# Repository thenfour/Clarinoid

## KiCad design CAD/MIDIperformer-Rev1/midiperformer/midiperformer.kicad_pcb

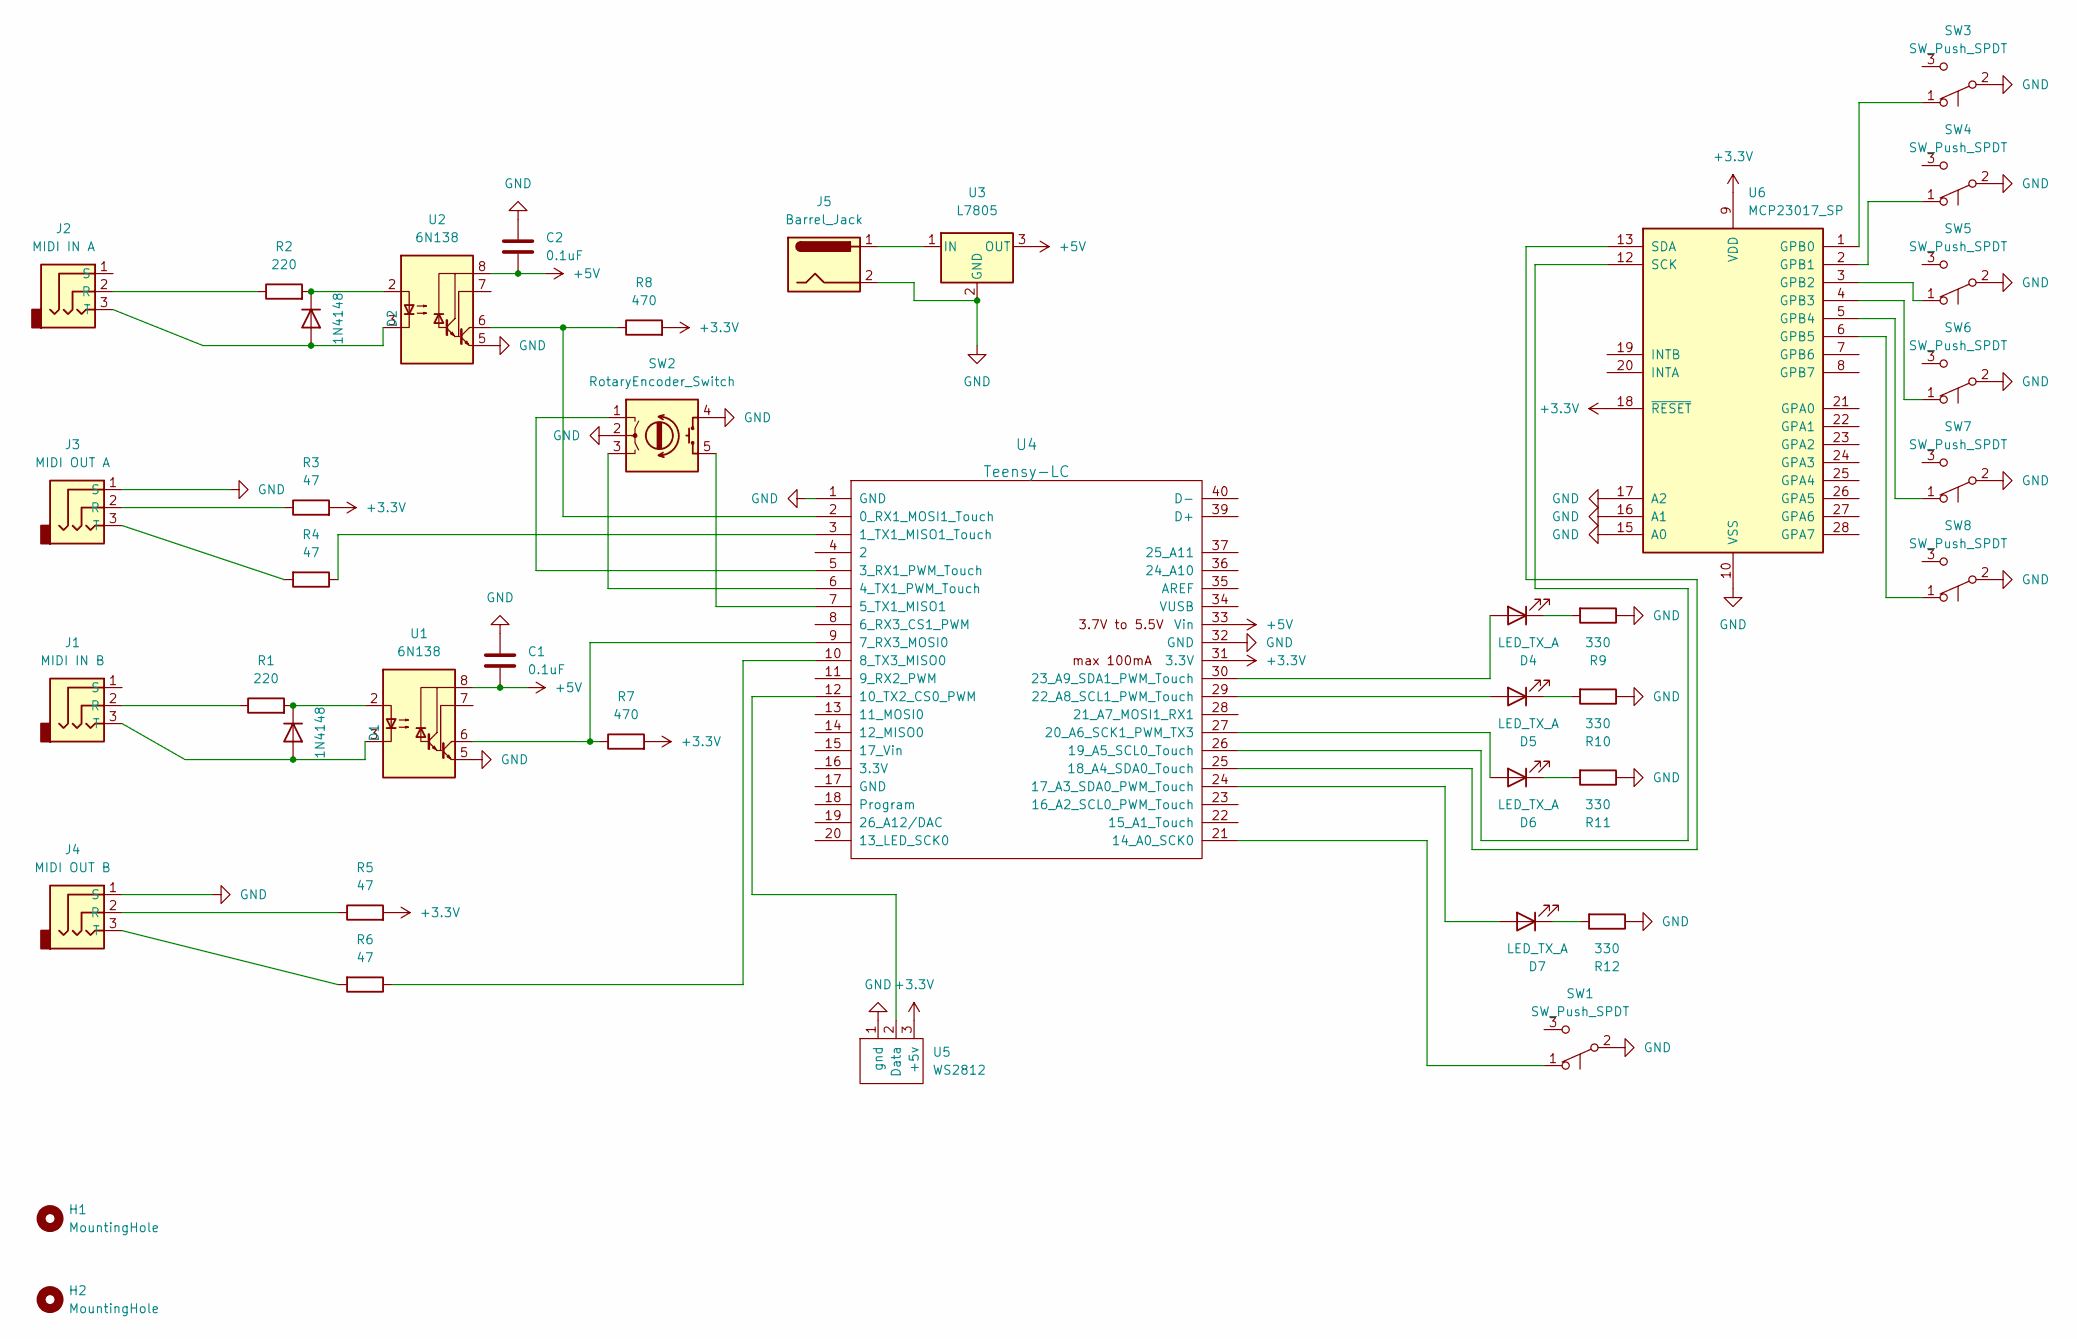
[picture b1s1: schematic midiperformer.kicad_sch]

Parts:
C1, C2: 0.1uF; C_Disc_D3.8mm_W2.6mm_P2.50mm
D1, D2: 1N4148; D_DO-35_SOD27_P7.62mm_Horizontal
D4, D5, D6, D7: LED_TX_A; SolderWire-0.25sqmm_1x02_P4.2mm_D0.65mm_OD1.7mm
H1, H2: MountingHole; MountingHole_2.7mm_M2.5_ISO14580_Pad
J1: MIDI IN B; SolderWire-0.25sqmm_1x03_P4.2mm_D0.65mm_OD1.7mm
J2: MIDI IN A; SolderWire-0.25sqmm_1x03_P4.2mm_D0.65mm_OD1.7mm
J3: MIDI OUT A; SolderWire-0.25sqmm_1x03_P4.2mm_D0.65mm_OD1.7mm
J4: MIDI OUT B; SolderWire-0.25sqmm_1x03_P4.2mm_D0.65mm_OD1.7mm
J5: Barrel_Jack; SolderWire-0.25sqmm_1x02_P4.2mm_D0.65mm_OD1.7mm
R1, R2: 220; R_Axial_DIN0207_L6.3mm_D2.5mm_P10.16mm_Horizontal
R3, R4, R5, R6: 47; R_Axial_DIN0207_L6.3mm_D2.5mm_P10.16mm_Horizontal
R7, R8: 470; R_Axial_DIN0207_L6.3mm_D2.5mm_P10.16mm_Horizontal
R9, R10, R11, R12: 330; R_Axial_DIN0207_L6.3mm_D2.5mm_P10.16mm_Horizontal
SW1, SW3, SW4, SW5, SW6, SW7, SW8: SW_Push_SPDT; SolderWire-0.25sqmm_1x02_P4.5mm_D0.65mm_OD2mm
SW2: RotaryEncoder_Switch; SolderWire-0.25sqmm_1x05_P4.2mm_D0.65mm_OD1.7mm
U1, U2: 6N138; DIP-8_W7.62mm
U3: L7805; TO-220-3_Vertical
U4: Teensy-LC; Teensy_LC
U5: WS2812; SolderWire-0.25sqmm_1x03_P4.2mm_D0.65mm_OD1.7mm
U6: MCP23017_SP; DIP-28_W7.62mm

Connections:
+3V3: R3.2, R5.2, R7.2, R8.2, U4.31 (3.3V), U5.3 (+5v), U6.9 (VDD), U6.18 (~RESET)
+5V: C1.1, C2.1, U1.8 (VCC), U2.8 (VCC), U3.3 (OUT), U4.33 (Vin)
GND: C1.2, C2.2, J3.1 (S), J4.1 (S), J5.2, R9.1, R10.1, R11.1, R12.1, SW1.2 (B), SW2.2 (GND), SW2.4 (SWGND), SW3.2 (B), SW4.2 (B), SW5.2 (B), SW6.2 (B), SW7.2 (B), SW8.2 (B), U1.5 (GND), U2.5 (GND), U3.2 (GND), U4.1 (GND), U4.32 (GND), U5.1 (gnd), U6.10 (VSS), U6.15 (A0), U6.16 (A1), U6.17 (A2)
unnamed: D1.1 (K), R1.2, U1.2 (C1)
unnamed: D1.2 (A), J1.3 (T), U1.3 (C2)
unnamed: D2.1 (K), R2.2, U2.2 (C1)
unnamed: D2.2 (A), J2.3 (T), U2.3 (C2)
unnamed: D4.1 (K), R9.2
unnamed: D4.2 (A), U4.30 (23_A9_SDA1_PWM_Touch)
unnamed: D5.1 (K), R10.2
unnamed: D5.2 (A), U4.29 (22_A8_SCL1_PWM_Touch)
unnamed: D6.1 (K), R11.2
unnamed: D6.2 (A), U4.27 (20_A6_SCK1_PWM_TX3)
unnamed: D7.1 (K), R12.2
unnamed: D7.2 (A), U4.24 (17_A3_SDA0_PWM_Touch)
unnamed: J1.2 (R), R1.1
unnamed: J2.2 (R), R2.1
unnamed: J3.2 (R), R3.1
unnamed: J3.3 (T), R4.2
unnamed: J4.2 (R), R5.1
unnamed: J4.3 (T), R6.2
unnamed: J5.1, U3.1 (IN)
unnamed: R4.1, U4.3 (1_TX1_MISO1_Touch)
unnamed: R6.1, U4.10 (8_TX3_MISO0)
unnamed: R7.1, U1.6 (VO2), U4.9 (7_RX3_MOSI0)
unnamed: R8.1, U2.6 (VO2), U4.2 (0_RX1_MOSI1_Touch)
unnamed: SW1.1 (A), U4.21 (14_A0_SCK0)
unnamed: SW2.1 (A), U4.5 (3_RX1_PWM_Touch)
unnamed: SW2.3 (B), U4.6 (4_TX1_PWM_Touch)
unnamed: SW2.5 (SW), U4.7 (5_TX1_MISO1)
unnamed: SW3.1 (A), U6.1 (GPB0)
unnamed: SW4.1 (A), U6.2 (GPB1)
unnamed: SW5.1 (A), U6.3 (GPB2)
unnamed: SW6.1 (A), U6.4 (GPB3)
unnamed: SW7.1 (A), U6.5 (GPB4)
unnamed: SW8.1 (A), U6.6 (GPB5)
unnamed: U4.12 (10_TX2_CS0_PWM), U5.2 (Data)
unnamed: U4.25 (18_A4_SDA0_Touch), U6.13 (SDA)
unnamed: U4.26 (19_A5_SCL0_Touch), U6.12 (SCK)

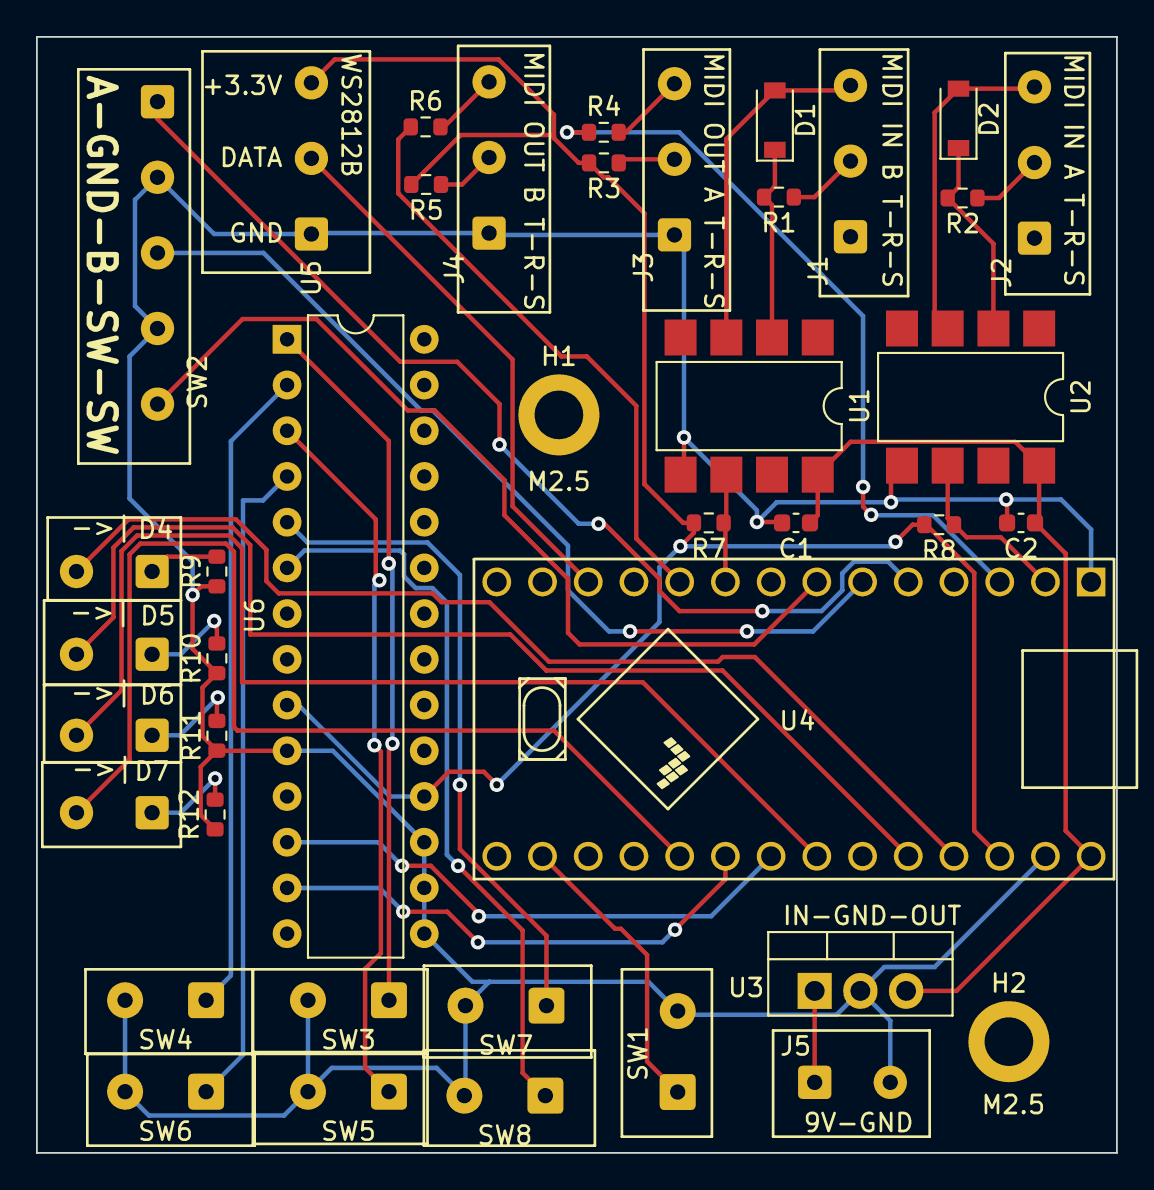
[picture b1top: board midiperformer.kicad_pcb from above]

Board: 2 copper layers, 60.0 x 62.0 mm, 41 parts (0 on the bottom side), 39 nets.

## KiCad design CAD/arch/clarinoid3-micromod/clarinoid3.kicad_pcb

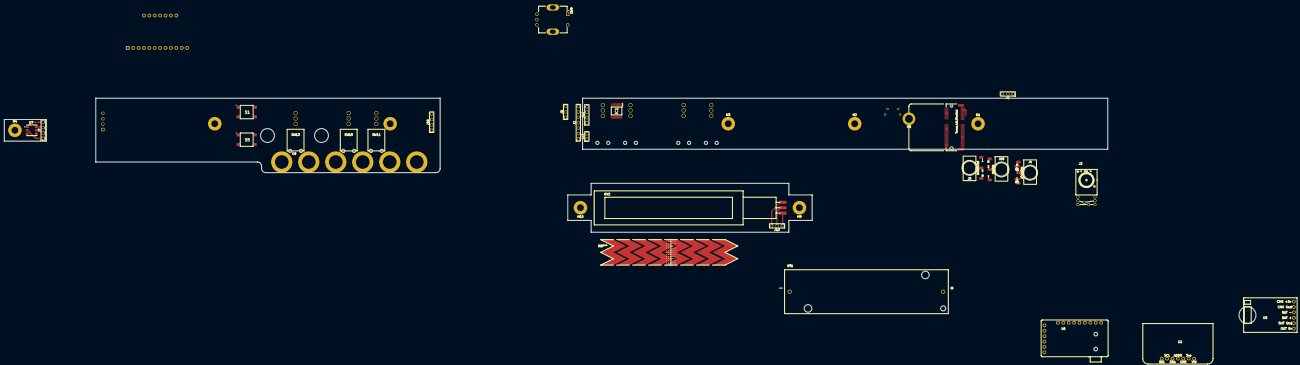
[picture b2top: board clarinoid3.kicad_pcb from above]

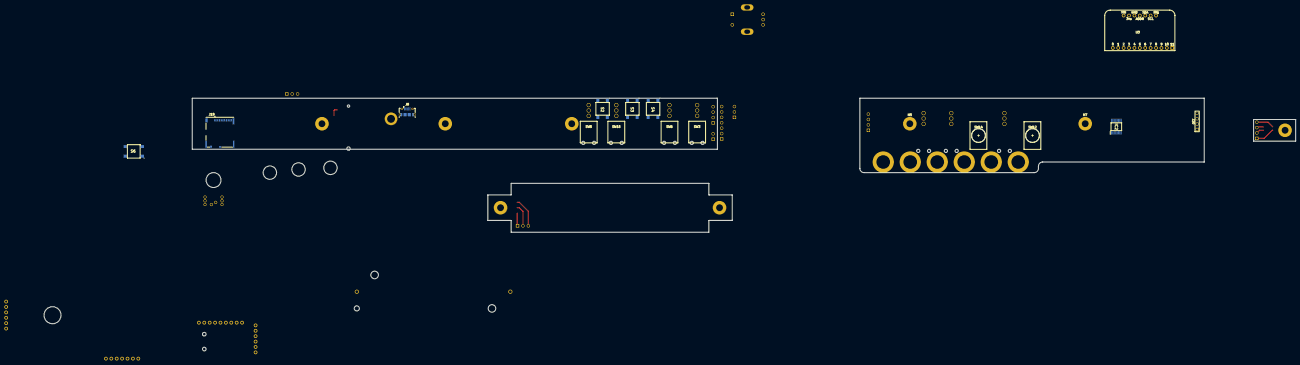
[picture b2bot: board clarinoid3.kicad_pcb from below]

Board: 2 copper layers, 519.0 x 63.0 mm, 53 parts (17 on the bottom side), 14 nets.

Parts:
BT1: Battery_Cell; KEYSTONE_1043
H1: rh_h1; MountingHole_3.2mm_M3_Pad
H2: rh_h2; MountingHole_3.2mm_M3_Pad
H3: rh_h3; MountingHole_3.2mm_M3_Pad
H4: breath_h1; MountingHole_3.2mm_M3_Pad
H5: lh_h1; MountingHole_3.2mm_M3_Pad
H7: lh_h2; MountingHole_3.2mm_M3_Pad
H8: micromod_spacer; Wurth_9774025151_M2.5_spacer_for_micromod
H9: pitch_h1; MountingHole_3.2mm_M3_Pad
H10: pitch_h2; MountingHole_3.2mm_M3_Pad
IC1, IC2: PCA9554APW,118; SOP65P640X110-16N
J1: LEDHdr; solder point DIP 1x3
J2: OLEDHdr; solder point DIP 1x7
J3: StereoPot_SW; Bourns_POT_PTR902-2020K-A103_PANEL
J4: MIDIOut; Switchcraft_35RAPC4BH3_3.5mm_female_jack_nosw_downfacing
J5: AudioOut; Switchcraft_35RAPC4BH3_3.5mm_female_jack_nosw_downfacing
J7: BREATHI2CHdr; solder point DIP 1x4
J8: USB_B_Micro; USB_Micro-B_Amphenol_10118194_Horizontal
J9: RH_PitchHdr; solder point DIP 1x3
J10: pitch_pitchhdr; solder point DIP 1x3
J12: RHI2CHdr; solder point DIP 1x4
J13: RHencHdr; solder point DIP 1x2
J16: LHI2CHdr; solder point DIP 1x4
J18: MIDIin; Switchcraft_35RAPC4BH3_3.5mm_female_jack_nosw_downfacing
J19: Molex microSD 503398-1892; MOLEX_503398-1892
J20: LH-BREATHI2CHdr; solder point DIP 1x4
R1, R2: 47; R_0603_1608Metric
RV2: PITCH; MAT060-B100K-231-A01
S1: LHxv1; B3FS-1000P
S2: RHxv1; B3FS-1000P
S3: RHxv2; B3FS-1000P
S4: RHxv3; B3FS-1000P
S5: LHxv2; B3FS-1000P
S6: charge_ind_btn; B3FS-1000P
SW3: RHx1; MB2511S2G45
SW5: RHx2; MB2511S2G45
SW6: RHx3; MB2511S2G45
SW9: Rotary_Encoder_Switch; Bourns_ENC_PEC11R-4215F-S0024
SW10: LHx1; MB2511S2G45
SW11: LHx2; MB2511S2G45
SW12: LHback; MB2511S4W01-BC
SW13: LHx3; MB2511S2G45
SW14: LHok; MB2511S4W01-BC
SW15: RHx4; MB2511S2G45
U1: Teensy_4.0_MicroMod; Teensy_4.0_MicroMod_nospacer
U2: AdafruitMPR121; MPR121_hdr_0keys_copy
U3: AdafruitMPR121; MPR121_hdr_12keys
U5: MH-CD42; MH-CD42_flip_window
U6: PCM5102; HILETGOPCM5102
U7: HoneywellABPMAND001PG2A3; SON160P500X500X140-6N
U8: octave_keys; CLARINOID_M6_6OCTAVES

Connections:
+3V3: J7.1, J10.1, J16.4, J20.1, RV2.1, U2.19 (Vin), U3.19 (Vin), U7.2 (Vs)
GND: J7.4, J10.3, J16.3, J20.4, RV2.3, S1.1 (COM_1), S2.3 (NO_1), S3.3 (NO_1), S4.3 (NO_1), S5.1 (COM_1), SW3.2, SW5.2, SW6.2, SW9.S2, SW10.2, SW11.2, SW13.2, SW15.2, U2.17 (GND), U3.17 (GND), U7.1 (GND)
unnamed: J10.2, RV2.2
unnamed: J19.6 (VSS), J19.9 (VSS)
unnamed: J19.P1 (SHIELD), J19.P2 (SHIELD), J19.P3 (SHIELD), J19.P4 (SHIELD)
unnamed: U3.4, U8.6
unnamed: U3.5, U8.5
unnamed: U3.6, U8.4
unnamed: U3.7, U8.3
unnamed: U3.8, U8.2
unnamed: U3.9, U8.1
unnamed: U3.16 (Addr), U3.18 (3vo)
i2c_scl: J7.3, J16.1, J20.3, U2.14 (SCL), U3.14 (SCL), U7.6 (SCL)
i2c_sda: J7.2, J16.2, J20.2, U2.15 (SDA), U3.15 (SDA), U7.5 (SDA)

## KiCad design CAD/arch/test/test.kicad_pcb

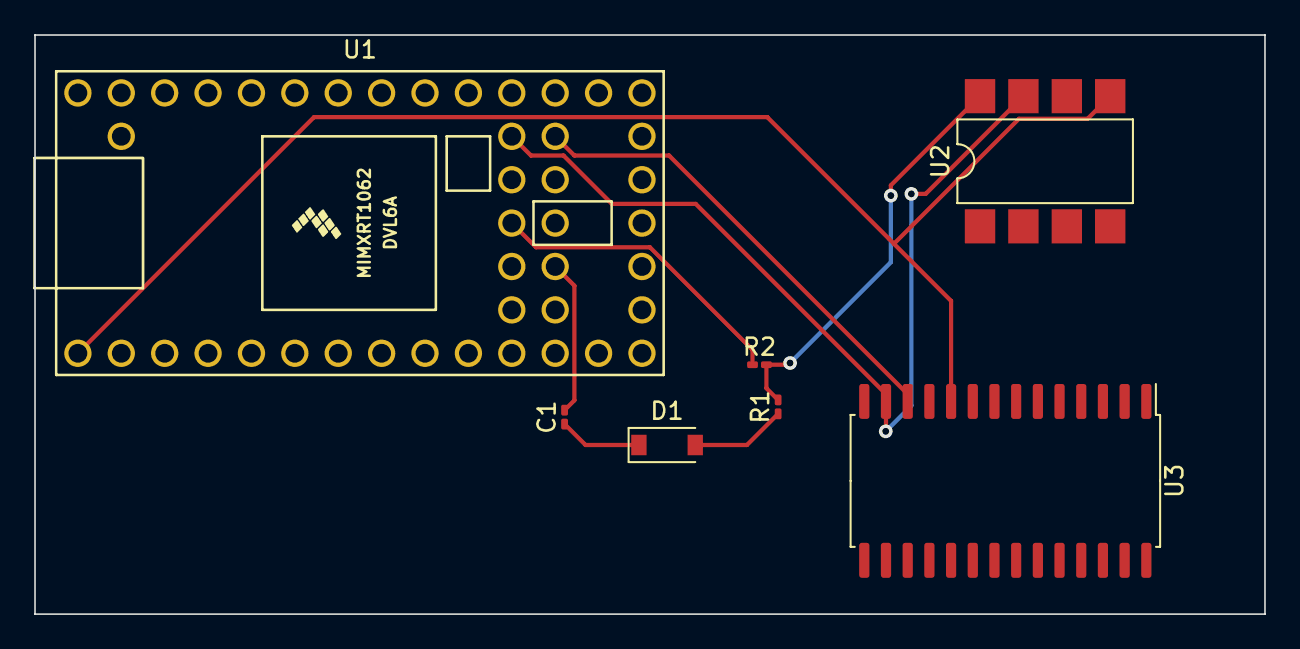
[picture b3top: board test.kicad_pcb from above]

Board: 2 copper layers, 72.0 x 33.9 mm, 7 parts (0 on the bottom side), 8 nets.

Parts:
C1: 0.1uF; C_0201_0603Metric_Pad0.64x0.40mm_HandSolder
D1: 1N4148; D_SOD-123
R1: 100; R_0201_0603Metric_Pad0.64x0.40mm_HandSolder
R2: 47; R_0201_0603Metric_Pad0.64x0.40mm_HandSolder
U1: Teensy4.0; Teensy40
U2: 6N138; SMDIP-8_W7.62mm
U3: MCP23017_SO; SOIC-28W_7.5x17.9mm_P1.27mm

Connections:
GND: U1.1 (GND), U2.5 (GND), U3.10 (VSS)
unnamed: C1.1, D1.1 (K)
unnamed: C1.2, U1.41 (30_CRX3)
unnamed: D1.2 (A), R1.1
unnamed: R2.1, U1.40 (29_TX7)
unnamed: U1.35 (24_A10_TX6_SCL2), U3.12 (SCK)
unnamed: U1.36 (25_A11_RX6_SDA2), U2.7 (VO1), U3.13 (SDA)
unnamed: R1.2, R2.2, U2.8 (VCC)

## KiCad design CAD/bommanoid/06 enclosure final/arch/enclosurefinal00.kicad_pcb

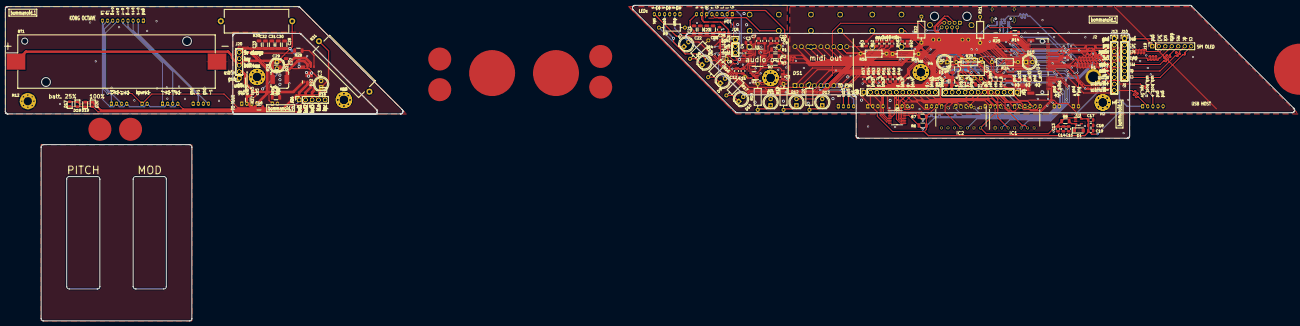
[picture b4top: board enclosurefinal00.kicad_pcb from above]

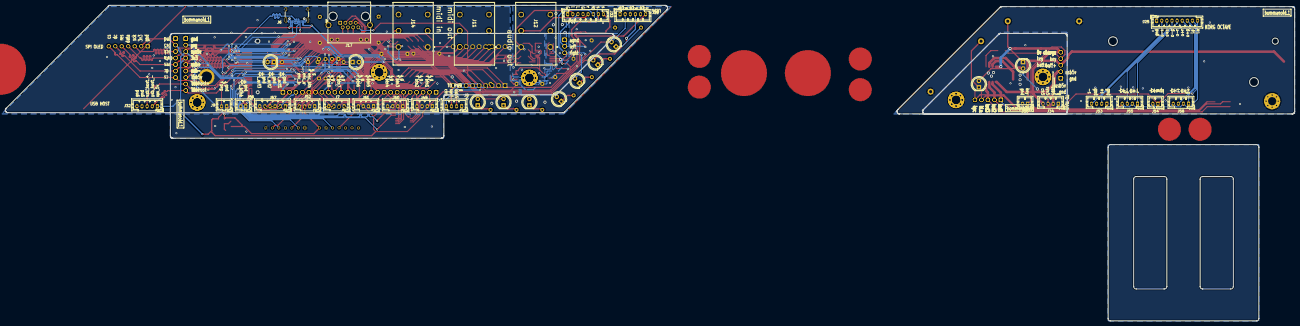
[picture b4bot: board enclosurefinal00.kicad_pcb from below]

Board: 2 copper layers, 504.6 x 123.5 mm, 166 parts (24 on the bottom side), 191 nets.

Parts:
BT1: Battery_Cell; BatteryHolder_Keystone_1042_1x18650
C1, C6, C7, C11, C13: 10uF; C_0805_2012Metric
C2, C9, C10, C12, C15, C19, C25: 0.1uF; C_0805_2012Metric
C3, C4, C5, C8: 2.2uF; C_0805_2012Metric
C14, C18: 0.22uF; C_0805_2012Metric
C16, C26: 10uF; C_1206_3216Metric
C17: 1uF; C_0805_2012Metric
C20, C33: 0.1uF; C_1206_3216Metric
C21, C22, C23, C24, C27, C28, C29, C30, C31, C32: 22uF; C_1206_3216Metric
D1: 3.3v; D_MiniMELF
D2: 1N4148WS; D_SOD-323
D7, D8, D9, D10, D11, D12, D13, D14, D15, D21, D22: LED; LED_D5.0mm_withbottomtext
D16: korgpwr; LED_0805_2012Metric
D17: 25%; LED_0805_2012Metric
D18: 50%; LED_0805_2012Metric
D19: 75%; LED_0805_2012Metric
D20: 100%; LED_0805_2012Metric
DS1: PDC54-11GWA; DIPS1524W75P254L2520H805Q18N
H1: M.2 riser 2.5mm; Sinhoo SMTSO2530CTJ
H2, H3, H4, H5, H6, H7, H8, H9, H10, H11, H12: MountingHole_Pad; MountingHole_3.2mm_M3_Pad_Via
IC1, IC2: SN74AHCT125N; DIP794W53P254L1930H508Q14N
IC3: Injoinic IP5306 battery charge; SOIC127P599X155-9N (IP5306)
J1: Conn_01x07; PinHeader_1x07_P2.54mm_Vertical
J2: Conn_01x09; PinHeader_1x09_P2.54mm_Vertical
J3, J4: Conn_01x12; PinHeader_1x12_P2.54mm_Vertical
J5: Conn_01x03; PinHeader_1x03_P2.54mm_Vertical
J6: XKB_U262-16XN-4BVC11 USB-C recept; USB_C_Receptacle_XKB_U262-16XN-4BVC11
J7, J8, J34, J49, J50, J51, J52, J53, J55, J58: Conn_01x04; JST_PH_B4B-PH-K_1x04_P2.00mm_Vertical
J9, J26, J54, J56: Conn_01x02; JST_PH_B2B-PH-K_1x02_P2.00mm_Vertical
J10, J19: Conn_01x07; PinSocket_1x07_P2.54mm_Vertical
J11, J12, J14: Amphenol ACJS-MHOM; ACJSMHOM
J13: Conn_01x09; PinSocket_1x09_P2.54mm_Vertical
J15, J16: Conn_01x12; PinSocket_1x12_P2.54mm_Vertical
J17: RJ45_LED_Shielded; RJ45_Amphenol_RJHSE538X
J18: Conn_01x03; PinSocket_1x03_P2.54mm_Vertical
J20, J21, J23, J24: Conn_01x05; PinSocket_1x05_P2.54mm_Vertical
J22, J57: Conn_01x06; JST_PH_B6B-PH-K_1x06_P2.00mm_Vertical
J25: Conn_01x09; JST_PH_B9B-PH-K_1x09_P2.00mm_Vertical
J32: USB_A; JST_PH_B5B-PH-K_1x05_P2.00mm_Vertical
J33: Conn_01x08; JST_PH_B8B-PH-K_1x08_P2.00mm_Vertical
L1: 1uH-psa; Inductor_MCS0630-1R0MN2
NT1: NetTie_2; NetTie-2_SMD_Pad0.5mm
NT4, NT5: NetTie_2; NetTie-2_SMD_Pad1.0mm
R1, R2, R3: 22R; R_1206_3216Metric
R4, R5, R11: 470R; R_1206_3216Metric
R6, R7: 4.7k; R_1206_3216Metric
R8: 100k; R_1206_3216Metric
R9, R15, R16, R17, R18, R19, R20, R21, R22, R23, R24, R55, R56: R; R_Axial_DIN0207_L6.3mm_D2.5mm_P10.16mm_Horizontal
R10: 220R; R_1206_3216Metric
R12, R13: 47R; R_1206_3216Metric
R14, R25: 5.1k; R_1206_3216Metric
R27: 2R; R_1206_3216Metric
R28: 10k; R_1206_3216Metric
R29: 0.5R; R_1206_3216Metric
R30, R31: R; R_Axial_Power_L25.0mm_W9.0mm_P27.94mm
R47, R48, R49, R50, R51, R52, R53, R54, R57, R58, R59, R60, R61, R62, R63: 220; R_0805_2012Metric
U1: PCM5102A; TSSOP-20_4.4x6.5mm_P0.65mm
U2, U3: TLV75733PDBV; SOT-23-5
U4: APCI0108-P001A Teensy_4.0_MicroMod; APCI0108-P001A M.2 MicroMod 21992304
U5: TCA9554PW; TSSOP-16_4.4x5mm_P0.65mm
U6: Micromod outline; Teensy_4.0_MicroMod outline fab
U7: 6N138; DIP-8_W7.62mm
U8: ssd1306_graphic; SSD1306_128x64_approximate

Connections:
/bommanoid_batt_bottom/5v_charge_outp: J23.5, J34.4
/bommanoid_batt_bottom/batt+: BT1.1 (+), J23.3
/bommanoid_batt_bottom/chargeled_1: D17.2 (A), D18.1 (K), J24.1
/bommanoid_batt_bottom/chargeled_2: D19.2 (A), D20.1 (K), J24.2
/bommanoid_batt_bottom/chargeled_3: D17.1 (K), D18.2 (A), D19.1 (K), D20.2 (A), J24.3
/bommanoid_batt_bottom/gnd: BT1.2 (-), H10.1, H11.1, H12.1, J23.1, J25.1, J26.2, J34.1, J53.1, J53.3, R30.2, R31.2
/bommanoid_batt_bottom/key: J23.4, J26.1
/bommanoid_batt_bottom/korg_led_anode: J24.4, J25.9, J54.2, J55.2, J55.4, J58.2, J58.4
/bommanoid_batt_bottom/korg_power_led_cathode: J24.5, J25.8, J54.1
/bommanoid_batt_bottom/oct_down_green_cathode: J25.4, J55.3
/bommanoid_batt_bottom/oct_down_red_cathode: J25.5, J55.1
/bommanoid_batt_bottom/oct_down_sw: J25.2, J53.4
/bommanoid_batt_bottom/oct_up_green_cathode: J25.7, J58.1
/bommanoid_batt_bottom/oct_up_red_cathode: J25.6, J58.3
/bommanoid_batt_bottom/oct_up_sw: J25.3, J53.2
/bommanoid_batt_bottom/sys_5v: D21.2 (A), D22.2 (A), J34.3
/bommanoid_batt_bottom/usb_5v: J23.2, J34.2
/bommanoid_batt_top/batt+: C29.1, J20.3, L1.2, R29.1
/bommanoid_batt_top/chargeled_1: IC3.2 (LED1), J21.1
/bommanoid_batt_top/chargeled_2: IC3.3 (LED2), J21.2
/bommanoid_batt_top/chargeled_3: IC3.4 (LED3), J21.3
/bommanoid_batt_top/charger output +5v: C28.1, C30.1, C31.1, C32.1, C33.1, IC3.8 (VOUT), J20.5
/bommanoid_batt_top/gnd: C16.2, C26.2, C27.2, C28.2, C29.2, C30.2, C31.2, C32.2, C33.2, H8.1, H9.1, IC3.9 (PWR-GND), J20.1
/bommanoid_batt_top/key: J20.4, R28.2
/bommanoid_batt_top/korg_power_led_anode: D16.2 (A), J21.4
/bommanoid_batt_top/korg_power_led_cathode: D16.1 (K), J21.5
/bommanoid_batt_top/usb_5v: C26.1, IC3.1 (VIN), J20.2, R27.1
/bommanoid_main_bottom/3v3: J10.2, J13.4, J19.2
/bommanoid_main_bottom/agnd: H7.1, J12.3 (S_1), J12.4 (S_2), J18.1, J33.1, J33.4
/bommanoid_main_bottom/aleft_post_pot: J12.6 (T), J33.2
/bommanoid_main_bottom/aleft_pre_pot: J18.2, J33.3
/bommanoid_main_bottom/amp_5v: D7.2 (A), J17.8, J22.2
/bommanoid_main_bottom/aright_post_pot: J12.5 (R), J33.5
/bommanoid_main_bottom/aright_pre_pot: J18.3, J33.6
/bommanoid_main_bottom/btn_x1: J16.2, J49.2
/bommanoid_main_bottom/btn_x2: J16.3, J49.4
/bommanoid_main_bottom/btn_x3: J16.4, J50.2
/bommanoid_main_bottom/btn_x4: J16.5, J50.4
/bommanoid_main_bottom/btn_x5: J16.6, J51.2
/bommanoid_main_bottom/btn_x6: J16.7, J51.4
/bommanoid_main_bottom/btn_x7: J7.2, J16.8
/bommanoid_main_bottom/btn_x8: J7.4, J16.9
/bommanoid_main_bottom/chargeoutp_5v: J8.4, NT4.2
/bommanoid_main_bottom/enc_a: J16.11, J52.3
/bommanoid_main_bottom/enc_b: J16.12, J52.4
/bommanoid_main_bottom/enc_btn: J16.10, J52.2
/bommanoid_main_bottom/gnd: C21.2, C22.2, C23.2, C24.2, C25.2, H5.1, H6.1, J6.A1 (GND), J6.A12 (GND), J6.B1 (GND), J6.B12 (GND), J6.S1 (SHIELD), J7.1, J7.3, J8.1, J9.1, J10.1, J11.3 (S_1), J11.4 (S_2), J13.1, J14.3 (S_1), J14.4 (S_2), J15.1, J16.1, J17.1, J17.SH, J19.1, J22.1, J22.3, J22.5, J32.4 (GND), J32.5 (Shield), J49.1, J49.3, J50.1, J50.3, J51.1, J51.3, J52.1, J56.1, J57.1, J57.3, J57.5, R9.2, R14.1, R15.2, R16.2, R17.2, R18.2, R19.2, R20.2, R21.1, R22.1, R23.2, R24.2, R25.1
/bommanoid_main_bottom/led_act1_5v: D11.2 (A), J15.3, J17.5, J57.2
/bommanoid_main_bottom/led_act2_5v: D12.2 (A), J15.4, J17.6, J57.4
/bommanoid_main_bottom/led_act3_5v: D13.2 (A), J15.5, J17.7, J57.6
/bommanoid_main_bottom/led_blink_5v: D10.2 (A), J15.2, J17.4, J56.2
/bommanoid_main_bottom/led_rj45_green_5v: J15.7, J17.12
/bommanoid_main_bottom/led_rj45_yellow_5v: J15.6, J17.10
/bommanoid_main_bottom/midi_in_ring: J14.5 (R), J15.9
/bommanoid_main_bottom/midi_in_tip: J14.6 (T), J15.10
/bommanoid_main_bottom/midi_out_ring: J11.5 (R), J15.11
/bommanoid_main_bottom/midi_out_tip: J11.6 (T), J15.12
/bommanoid_main_bottom/oled_cs: J10.7, J19.7
/bommanoid_main_bottom/oled_data: J10.4, J19.4
/bommanoid_main_bottom/oled_dc: J10.6, J19.6
/bommanoid_main_bottom/oled_rst: J10.5, J19.5
/bommanoid_main_bottom/oled_sck: J10.3, J19.3
/bommanoid_main_bottom/pot_sw1: J33.7, NT4.1
/bommanoid_main_bottom/pot_sw2: C21.1, C22.1, C23.1, C24.1, C25.1, J33.8, NT5.1
/bommanoid_main_bottom/prg: J9.2, J13.2
/bommanoid_main_bottom/sys_5v: D9.2 (A), D14.2 (A), D15.2 (A), J8.3, J13.3, J17.2, J22.6, J32.1 (VBUS), NT5.2
/bommanoid_main_bottom/usb_5v: D8.2 (A), J6.A4 (VBUS), J6.A9 (VBUS), J6.B4 (VBUS), J6.B9 (VBUS), J8.2, J13.7, J22.4
/bommanoid_main_bottom/usb_data_+: J6.A6 (D+), J6.B6 (D+_to_A6), J13.5
/bommanoid_main_bottom/usb_data_-: J6.A7 (D-), J6.B7 (D-_to_A7), J13.6
/bommanoid_main_bottom/usb_host_+: J13.8, J32.3 (D+)
/bommanoid_main_bottom/usb_host_-: J13.9, J32.2 (D-)
/bommanoid_main_bottom/ws2812_data_5v: J15.8, J17.3
/bommanoid_main_top/3v3: C1.1, C2.1, C17.1, C18.1, C19.1, J1.2, J2.4, NT1.1, R6.2, R7.2, R11.1, R12.2, U3.5 (OUT), U4.2 (3.3v), U5.16 (VDD)
/bommanoid_main_top/I2C_SCL: R6.1, U4.14 (19_SCL_A5), U5.14 (SCL)
/bommanoid_main_top/I2C_SDA: R7.1, U4.12 (18_SDA_A4), U5.15 (SDA)
/bommanoid_main_top/I2S_BCK_MM: R3.1, U4.50 (21_BCLK_A7)
/bommanoid_main_top/I2S_DIN_MM: R2.1, U4.56 (7_AUD_OUT)
/bommanoid_main_top/I2S_LRCK_MM: R1.1, U4.52 (20_LRCLK_A6)
/bommanoid_main_top/LD_dig1: R55.2, U4.53 (24_SCL1_A10)
/bommanoid_main_top/LD_dig2: R56.2, U4.58 (23_MCLK_A9)
/bommanoid_main_top/T00 MIDI IN: R11.2, U4.19 (0_RX1), U7.6 (VO2)
/bommanoid_main_top/T01=MIDI OUT: R13.2, U4.17 (1_TX1)
/bommanoid_main_top/a3v3: C11.1, C12.1, U1.1 (CPVDD), U1.8 (AVDD), U2.5 (OUT)
/bommanoid_main_top/agnd: C5.2, C8.2, C11.2, C12.2, H3.1, J5.1, U1.9 (AGND)
/bommanoid_main_top/aleft: C5.1, J5.2, R4.2
/bommanoid_main_top/aright: C8.1, J5.3, R5.2
/bommanoid_main_top/btn_x1: J4.2, U5.7 (P3)
/bommanoid_main_top/btn_x2: J4.3, U5.6 (P2)
/bommanoid_main_top/btn_x3: J4.4, U5.5 (P1)
/bommanoid_main_top/btn_x4: J4.5, U5.4 (P0)
/bommanoid_main_top/btn_x5: J4.6, U5.9 (P4)
/bommanoid_main_top/btn_x6: J4.7, U5.10 (P5)
/bommanoid_main_top/btn_x7: J4.8, U5.11 (P6)
/bommanoid_main_top/btn_x8: J4.9, U5.12 (P7)
/bommanoid_main_top/d3v3: C7.2, C10.2, NT1.2, U1.17 (XSMT), U1.20 (DVDD), U2.1 (IN), U2.3 (EN)
/bommanoid_main_top/enc_a: J4.11, U4.43 (31_CAN_TX)
/bommanoid_main_top/enc_b: J4.12, U4.41 (30_CAN_RX)
/bommanoid_main_top/enc_btn: J4.10, U4.47 (2_PWM1)
/bommanoid_main_top/gnd: C1.2, C2.2, C6.2, C7.1, C9.2, C10.1, C13.2, C14.2, C15.2, C17.2, C18.2, C19.2, C20.2, D1.2 (A), H1.1, H2.1, H4.1, IC1.1 (1~OE), IC1.4 (2~OE), IC1.7 (GND), IC1.10 (3~OE), IC1.13 (4~OE), IC2.1 (1~OE), IC2.4 (2~OE), IC2.7 (GND), IC2.13 (4~OE), J1.1, J2.1, J3.1, J4.1, U1.10 (DEMP), U1.11 (FLT), U1.16 (FMT), U1.19 (DGND), U2.2 (GND), U3.2 (GND), U4.1 (GND), U4.7 (GND), U4.33 (GND), U4.36 (GND), U4.39 (GND), U4.45 (GND), U4.75 (GND), U5.1 (A0), U5.2 (A1), U5.3 (A2), U5.8 (GND), U7.5 (GND)
/bommanoid_main_top/ld_a: R62.2, U4.71 (6_G6)
/bommanoid_main_top/ld_b: R63.2, U4.73 (45_G5)
/bommanoid_main_top/ld_c: R57.1, U4.22 (17_TX2_A3)
/bommanoid_main_top/ld_d: R53.1, U4.38 (15_A1)
/bommanoid_main_top/ld_dp: R54.1, U4.32 (3_PWM0)
/bommanoid_main_top/ld_e: R48.1, U4.49 (22_BATT_VIN_A8)
/bommanoid_main_top/ld_f: R47.1, U4.63 (33_G10_ADCD+)
/bommanoid_main_top/ld_g: R58.2, U4.60 (36_SDIO_CLK)
/bommanoid_main_top/ld_h: R59.2, U4.65 (32_G9_ADCD-)
/bommanoid_main_top/ld_j: R60.2, U4.67 (26_G8_A12)
/bommanoid_main_top/ld_k: R52.1, U4.44 (42_G2)
/bommanoid_main_top/ld_l: R51.1, U4.46 (43_G3)
/bommanoid_main_top/ld_m: R50.1, U4.48 (44_G4)
/bommanoid_main_top/ld_n: R49.1, U4.51 (25_SDA1_A11)
/bommanoid_main_top/ld_p: R61.2, U4.69 (9_G7)
/bommanoid_main_top/led_act1_3v3: IC1.12 (4A), U4.8 (27_G11_A13)
/bommanoid_main_top/led_act1_5v: IC1.11 (4Y), J3.3
/bommanoid_main_top/led_act2_3v3: IC1.5 (2A), U4.20 (16_RX2_A2)
/bommanoid_main_top/led_act2_5v: IC1.6 (2Y), J3.4
/bommanoid_main_top/led_act3_3v3: IC1.2 (1A), U4.18 (5_D1)
/bommanoid_main_top/led_act3_5v: IC1.3 (1Y), J3.5
/bommanoid_main_top/led_blink_3v3: IC1.9 (3A), U4.4 (28_3.3vEN_GPIO)
/bommanoid_main_top/led_blink_5v: IC1.8 (3Y), J3.2
/bommanoid_main_top/led_rj45_green_3v3: IC2.5 (2A), U4.16 (29_I2C_INT)
/bommanoid_main_top/led_rj45_green_5v: IC2.6 (2Y), J3.7
/bommanoid_main_top/led_rj45_yellow_3v3: IC2.2 (1A), U4.10 (4_D0)
/bommanoid_main_top/led_rj45_yellow_5v: IC2.3 (1Y), J3.6
/bommanoid_main_top/midi_in_ring: J3.9, R10.1
/bommanoid_main_top/midi_in_tip: D2.2 (A), J3.10, U7.3 (C2)
/bommanoid_main_top/midi_out_ring: J3.11, R12.1
/bommanoid_main_top/midi_out_tip: J3.12, R13.1
/bommanoid_main_top/oled_cs: J1.7, U4.55 (10_SPI_CS)
/bommanoid_main_top/oled_data: J1.4, U4.59 (11_SPI_SDO)
/bommanoid_main_top/oled_dc: J1.6, U4.40 (40_G0)
/bommanoid_main_top/oled_rst: J1.5, U4.42 (41_G1)
/bommanoid_main_top/oled_sck: J1.3, U4.57 (13_SPI_SCK)
/bommanoid_main_top/prg: J2.2, U4.11 (PROGRAM)
/bommanoid_main_top/sys_5v: C13.1, C14.1, C15.1, C20.1, IC1.14 (VCC), IC2.14 (VCC), J2.3, R8.2, U3.1 (IN), U4.9 (VUSB), U7.8 (VCC)
/bommanoid_main_top/usb_data_+: J2.5, U4.3 (D+)
/bommanoid_main_top/usb_data_-: J2.6, U4.5 (D-)
/bommanoid_main_top/usb_host_+: J2.8, U4.35 (D+)
/bommanoid_main_top/usb_host_-: J2.9, U4.37 (D-)
/bommanoid_main_top/ws2812_data_1: IC2.11 (4Y), J3.8
/bommanoid_main_top/ws2812_data_3v3: IC2.12 (4A), U4.34 (14_A0)
unnamed: C3.1, U1.2 (CAPP)
unnamed: C3.2, U1.4 (CAPM)
unnamed: C4.1, U1.5 (VNEG)
unnamed: C4.2, U1.3 (CPGND)
unnamed: C6.1, C9.1, U1.18 (LDOO)
unnamed: C16.1, R27.2
unnamed: C27.1, IC3.6 (BAT), R29.2
unnamed: D1.1 (K), R8.1, U3.3 (EN)
unnamed: D2.1 (K), R10.2, U7.2 (C1)
unnamed: D7.1 (K), R9.1
unnamed: D8.1 (K), R15.1
unnamed: D9.1 (K), R16.1
unnamed: D10.1 (K), R17.1
unnamed: D11.1 (K), R18.1
unnamed: D12.1 (K), R19.1
unnamed: D13.1 (K), R20.1
unnamed: D14.1 (K), R23.1
unnamed: D15.1 (K), R24.1
unnamed: D21.1 (K), R30.1
unnamed: D22.1 (K), R31.1
unnamed: DS1.1 (ANODE_E), R48.2
unnamed: DS1.2 (ANODE_N), R49.2
unnamed: DS1.4 (ANODE_M), R50.2
unnamed: DS1.5 (ANODE_L), R51.2
unnamed: DS1.6 (ANODE_K), R52.2
unnamed: DS1.7 (ANODE_D), R53.2
unnamed: DS1.8 (ANODE_DP1/DP2), R54.2
unnamed: DS1.9 (ANODE_C), R57.2
unnamed: DS1.10 (ANODE_B), R63.1
unnamed: DS1.11 (COMMON_CATHODE_DIG_2), R56.1
unnamed: DS1.12 (ANODE_A), R62.1
unnamed: DS1.13 (ANODE_P), R61.1
unnamed: DS1.14 (ANODE_J), R60.1
unnamed: DS1.15 (ANODE_H), R59.1
unnamed: DS1.16 (COMMON_CATHODE_DIG_1), R55.1
unnamed: DS1.17 (ANODE_G), R58.1
unnamed: DS1.18 (ANODE_F), R47.2
unnamed: IC3.5 (KEY), R28.1
unnamed: IC3.7 (SW-inductor), L1.1
unnamed: J6.A5 (CC), R25.2
unnamed: J6.B5 (VCONN), R14.2
unnamed: J17.9, R21.2
unnamed: J17.11, R22.2
unnamed: R1.2, U1.15 (LRCK)
unnamed: R2.2, U1.14 (DIN)
unnamed: R3.2, U1.13 (BCK)
unnamed: R4.1, U1.6 (OUTL)
unnamed: R5.1, U1.7 (OUTR)
